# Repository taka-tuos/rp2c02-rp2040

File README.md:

# RP2C02 & RP2040 DevBoard

## 概要
RP2C02の限界が見たかったので作った

## 写真

## 部品
- 1 x Raspberry Pi Pico
- 1 x RP2C02
- 1 x Si5351Aモジュール(Adafruitタイプ、25MHz) or ピン互換の21.477272MHzモジュール(各自で作成)
- 1 x 2SA937
- 1 x 74HC573
- 1 x 62256 (<120ns)
- 2 x 100nF 2.54mm
- 1 x 22uF 5.0φ
- 1 x 470uF
- 1 x 150ohm
- 1 x 75ohm
- 1 x 820ohm
- 1 x RCAコネクタ

## なんでRP2040？
手元にあったのと流行りなので…

## レベル変換は？
- ADCピン以外は5.0Vまで耐えられるらしいので、それを信じることにした
- WRITEだけなら問題ない(割り込みピンはOpen-Drain駆動)

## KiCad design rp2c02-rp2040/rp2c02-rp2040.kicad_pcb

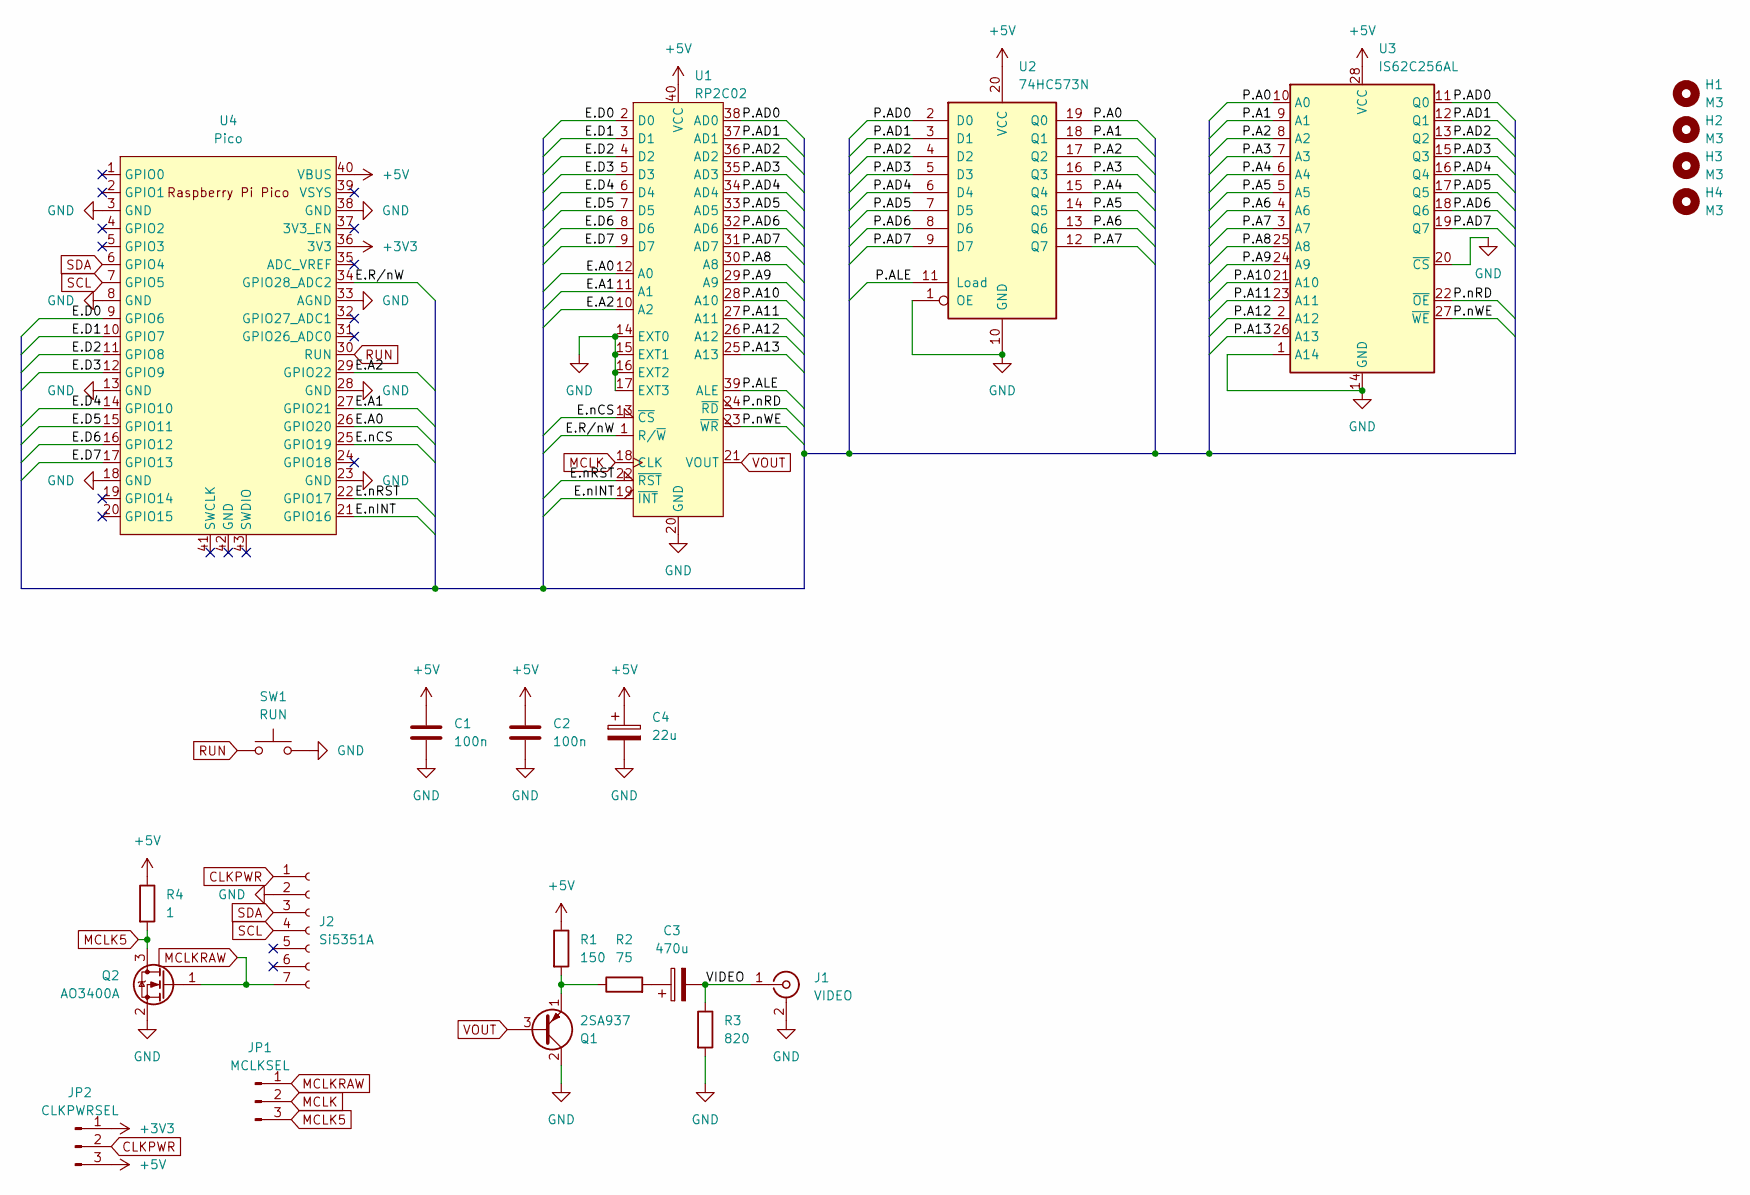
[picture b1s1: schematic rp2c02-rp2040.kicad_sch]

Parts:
C1, C2: 100n; C_Disc_D3.0mm_W1.6mm_P2.50mm
C3: 470u; CP_Radial_D10.0mm_P5.00mm
C4: 22u; CP_Radial_D5.0mm_P2.00mm
H1, H2, H3, H4: M3; MountingHole_3.2mm_M3
J1: VIDEO; CUI_RCJ-014
J2: Si5351A; PinSocket_1x07_P2.54mm_Vertical
JP1: MCLKSEL; PinHeader_1x03_P2.54mm_Vertical
JP2: CLKPWRSEL; PinHeader_1x03_P2.54mm_Vertical
Q1: 2SA937; PinSocket_1x03_P2.54mm_Vertical
Q2: AO3400A; SOT-23
R1: 150; R_Axial_DIN0207_L6.3mm_D2.5mm_P10.16mm_Horizontal
R2: 75; R_Axial_DIN0207_L6.3mm_D2.5mm_P10.16mm_Horizontal
R3: 820; R_Axial_DIN0207_L6.3mm_D2.5mm_P10.16mm_Horizontal
R4: 1; R_0805_2012Metric_Pad1.20x1.40mm_HandSolder
SW1: RUN; SW_PUSH_6mm
U1: RP2C02; DIP-40_W15.24mm_Socket
U2: 74HC573N; DIP-20_W7.62mm_Socket
U3: IS62C256AL; DIP-28_W15.24mm_Socket
U4: Pico; RPi_Pico_SMD_TH

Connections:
+3V3: JP2.1, U4.36 (3V3)
+5V: C1.1, C2.1, C4.1, JP2.3, R1.1, R4.1, U1.40 (VCC), U2.20 (VCC), U3.28 (VCC), U4.40 (VBUS)
/E.A0: U1.12 (A0), U4.26 (GPIO20)
/E.A1: U1.11 (A1), U4.27 (GPIO21)
/E.A2: U1.10 (A2), U4.29 (GPIO22)
/E.D0: U1.2 (D0), U4.9 (GPIO6)
/E.D1: U1.3 (D1), U4.10 (GPIO7)
/E.D2: U1.4 (D2), U4.11 (GPIO8)
/E.D3: U1.5 (D3), U4.12 (GPIO9)
/E.D4: U1.6 (D4), U4.14 (GPIO10)
/E.D5: U1.7 (D5), U4.15 (GPIO11)
/E.D6: U1.8 (D6), U4.16 (GPIO12)
/E.D7: U1.9 (D7), U4.17 (GPIO13)
/E.R/nW: U1.1 (R/~W), U4.34 (GPIO28_ADC2)
/E.nCS: U1.13 (~CS), U4.25 (GPIO19)
/E.nINT: U1.19 (~INT), U4.21 (GPIO16)
/E.nRST: U1.22 (~RST), U4.22 (GPIO17)
/P.A0: U2.19 (Q0), U3.10 (A0)
/P.A1: U2.18 (Q1), U3.9 (A1)
/P.A2: U2.17 (Q2), U3.8 (A2)
/P.A3: U2.16 (Q3), U3.7 (A3)
/P.A4: U2.15 (Q4), U3.6 (A4)
/P.A5: U2.14 (Q5), U3.5 (A5)
/P.A6: U2.13 (Q6), U3.4 (A6)
/P.A7: U2.12 (Q7), U3.3 (A7)
/P.A8: U1.30 (A8), U3.25 (A8)
/P.A9: U1.29 (A9), U3.24 (A9)
/P.A10: U1.28 (A10), U3.21 (A10)
/P.A11: U1.27 (A11), U3.23 (A11)
/P.A12: U1.26 (A12), U3.2 (A12)
/P.A13: U1.25 (A13), U3.26 (A13)
/P.AD0: U1.38 (AD0), U2.2 (D0), U3.11 (Q0)
/P.AD1: U1.37 (AD1), U2.3 (D1), U3.12 (Q1)
/P.AD2: U1.36 (AD2), U2.4 (D2), U3.13 (Q2)
/P.AD3: U1.35 (AD3), U2.5 (D3), U3.15 (Q3)
/P.AD4: U1.34 (AD4), U2.6 (D4), U3.16 (Q4)
/P.AD5: U1.33 (AD5), U2.7 (D5), U3.17 (Q5)
/P.AD6: U1.32 (AD6), U2.8 (D6), U3.18 (Q6)
/P.AD7: U1.31 (AD7), U2.9 (D7), U3.19 (Q7)
/P.ALE: U1.39 (ALE), U2.11 (Load)
/P.nRD: U1.24 (~RD), U3.22 (~OE)
/P.nWE: U1.23 (~WR), U3.27 (~WE)
/VIDEO: C3.2, J1.1 (In), R3.1
CLKPWR: J2.1, JP2.2
GND: C1.2, C2.2, C4.2, J1.2 (Ext), J2.2, Q1.2 (C), Q2.2 (S), R3.2, SW1.2, U1.14 (EXT0), U1.15 (EXT1), U1.16 (EXT2), U1.17 (EXT3), U1.20 (GND), U2.1 (OE), U2.10 (GND), U3.1 (A14), U3.14 (GND), U3.20 (~CS), U4.3 (GND), U4.8 (GND), U4.13 (GND), U4.18 (GND), U4.23 (GND), U4.28 (GND), U4.33 (AGND), U4.38 (GND)
MCLK: JP1.2, U1.18 (CLK)
MCLK5: JP1.3, Q2.3 (D), R4.2
MCLKRAW: J2.7, JP1.1, Q2.1 (G)
unnamed: C3.1, R2.2
unnamed: Q1.1 (E), R1.2, R2.1
RUN: SW1.1, U4.30 (RUN)
SCL: J2.4, U4.7 (GPIO5)
SDA: J2.3, U4.6 (GPIO4)
VOUT: Q1.3 (B), U1.21 (VOUT)

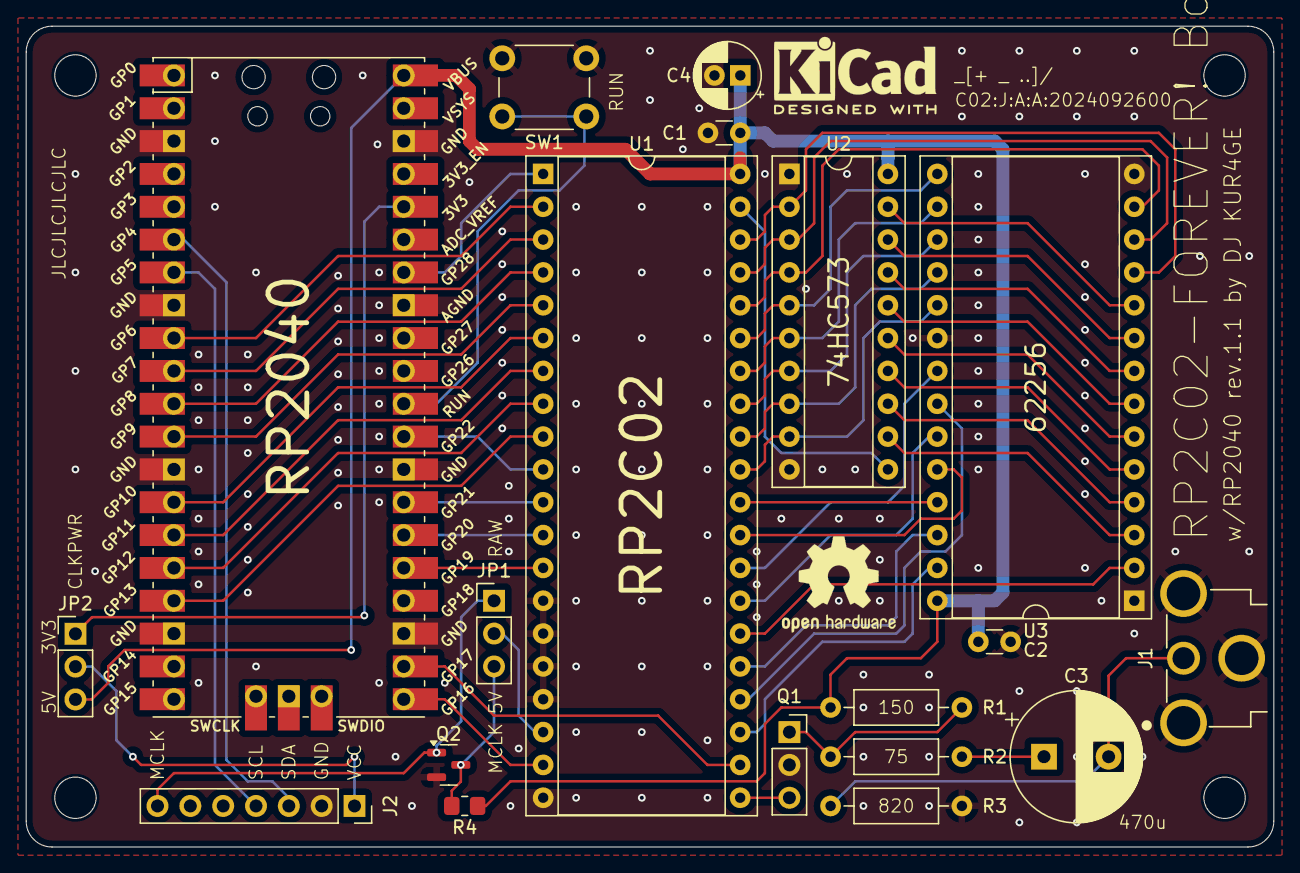
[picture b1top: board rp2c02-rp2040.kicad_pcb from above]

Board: 2 copper layers, 96.5 x 63.5 mm, 23 parts (0 on the bottom side), 54 nets.

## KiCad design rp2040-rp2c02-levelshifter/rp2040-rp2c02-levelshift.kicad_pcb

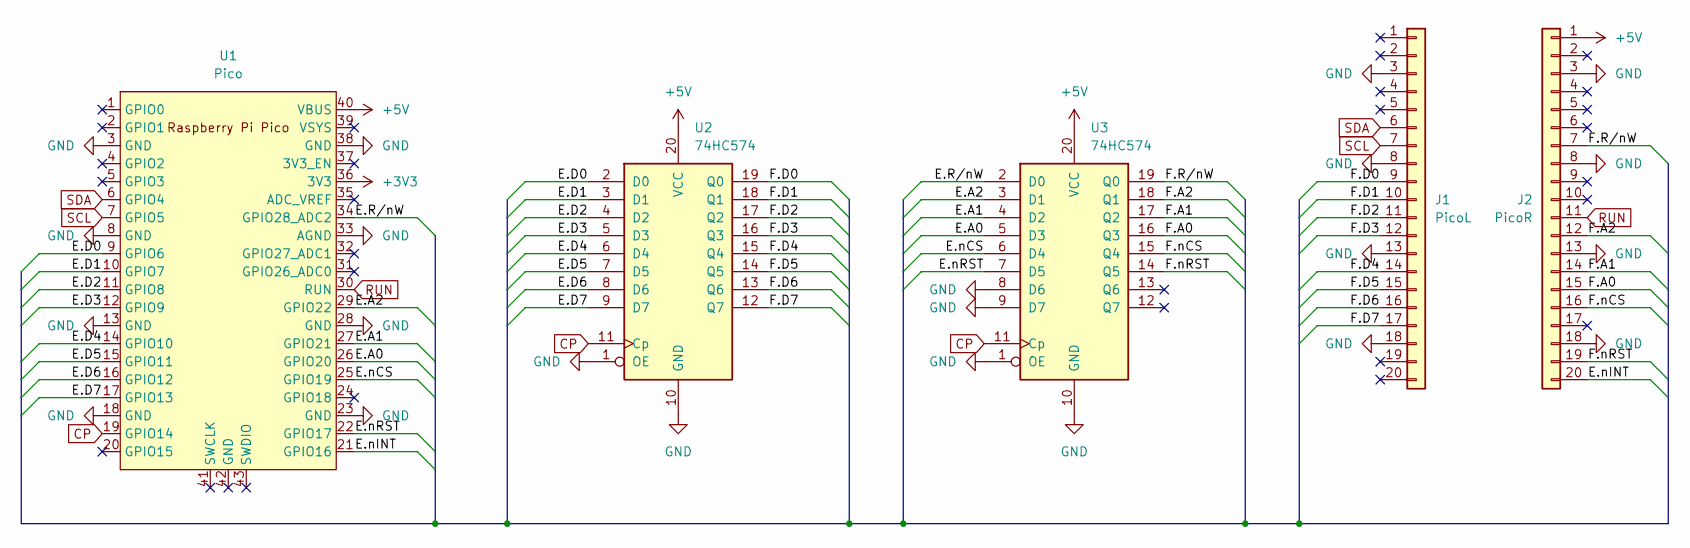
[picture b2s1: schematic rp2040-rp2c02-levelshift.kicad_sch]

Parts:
J1: PicoL; PinHeader_1x20_P2.54mm_Vertical
J2: PicoR; PinHeader_1x20_P2.54mm_Vertical
U1: Pico; RPi_Pico_SMD_TH
U2, U3: 74HC574; DIP-20_W7.62mm_Socket

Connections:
+3V3: U1.36 (3V3)
+5V: J2.1, U1.40 (VBUS), U2.20 (VCC), U3.20 (VCC)
/E.A0: U1.26 (GPIO20), U3.5 (D3)
/E.A1: U1.27 (GPIO21), U3.4 (D2)
/E.A2: U1.29 (GPIO22), U3.3 (D1)
/E.D0: U1.9 (GPIO6), U2.2 (D0)
/E.D1: U1.10 (GPIO7), U2.3 (D1)
/E.D2: U1.11 (GPIO8), U2.4 (D2)
/E.D3: U1.12 (GPIO9), U2.5 (D3)
/E.D4: U1.14 (GPIO10), U2.6 (D4)
/E.D5: U1.15 (GPIO11), U2.7 (D5)
/E.D6: U1.16 (GPIO12), U2.8 (D6)
/E.D7: U1.17 (GPIO13), U2.9 (D7)
/E.R/nW: U1.34 (GPIO28_ADC2), U3.2 (D0)
/E.nCS: U1.25 (GPIO19), U3.6 (D4)
/E.nINT: J2.20, U1.21 (GPIO16)
/E.nRST: U1.22 (GPIO17), U3.7 (D5)
/F.A0: J2.15, U3.16 (Q3)
/F.A1: J2.14, U3.17 (Q2)
/F.A2: J2.12, U3.18 (Q1)
/F.D0: J1.9, U2.19 (Q0)
/F.D1: J1.10, U2.18 (Q1)
/F.D2: J1.11, U2.17 (Q2)
/F.D3: J1.12, U2.16 (Q3)
/F.D4: J1.14, U2.15 (Q4)
/F.D5: J1.15, U2.14 (Q5)
/F.D6: J1.16, U2.13 (Q6)
/F.D7: J1.17, U2.12 (Q7)
/F.R/nW: J2.7, U3.19 (Q0)
/F.nCS: J2.16, U3.15 (Q4)
/F.nRST: J2.19, U3.14 (Q5)
CP: U1.19 (GPIO14), U2.11 (Cp), U3.11 (Cp)
GND: J1.3, J1.8, J1.13, J1.18, J2.3, J2.8, J2.13, J2.18, U1.3 (GND), U1.8 (GND), U1.13 (GND), U1.18 (GND), U1.23 (GND), U1.28 (GND), U1.33 (AGND), U1.38 (GND), U2.1 (OE), U2.10 (GND), U3.1 (OE), U3.8 (D6), U3.9 (D7), U3.10 (GND)
RUN: J2.11, U1.30 (RUN)
SCL: J1.7, U1.7 (GPIO5)
SDA: J1.6, U1.6 (GPIO4)

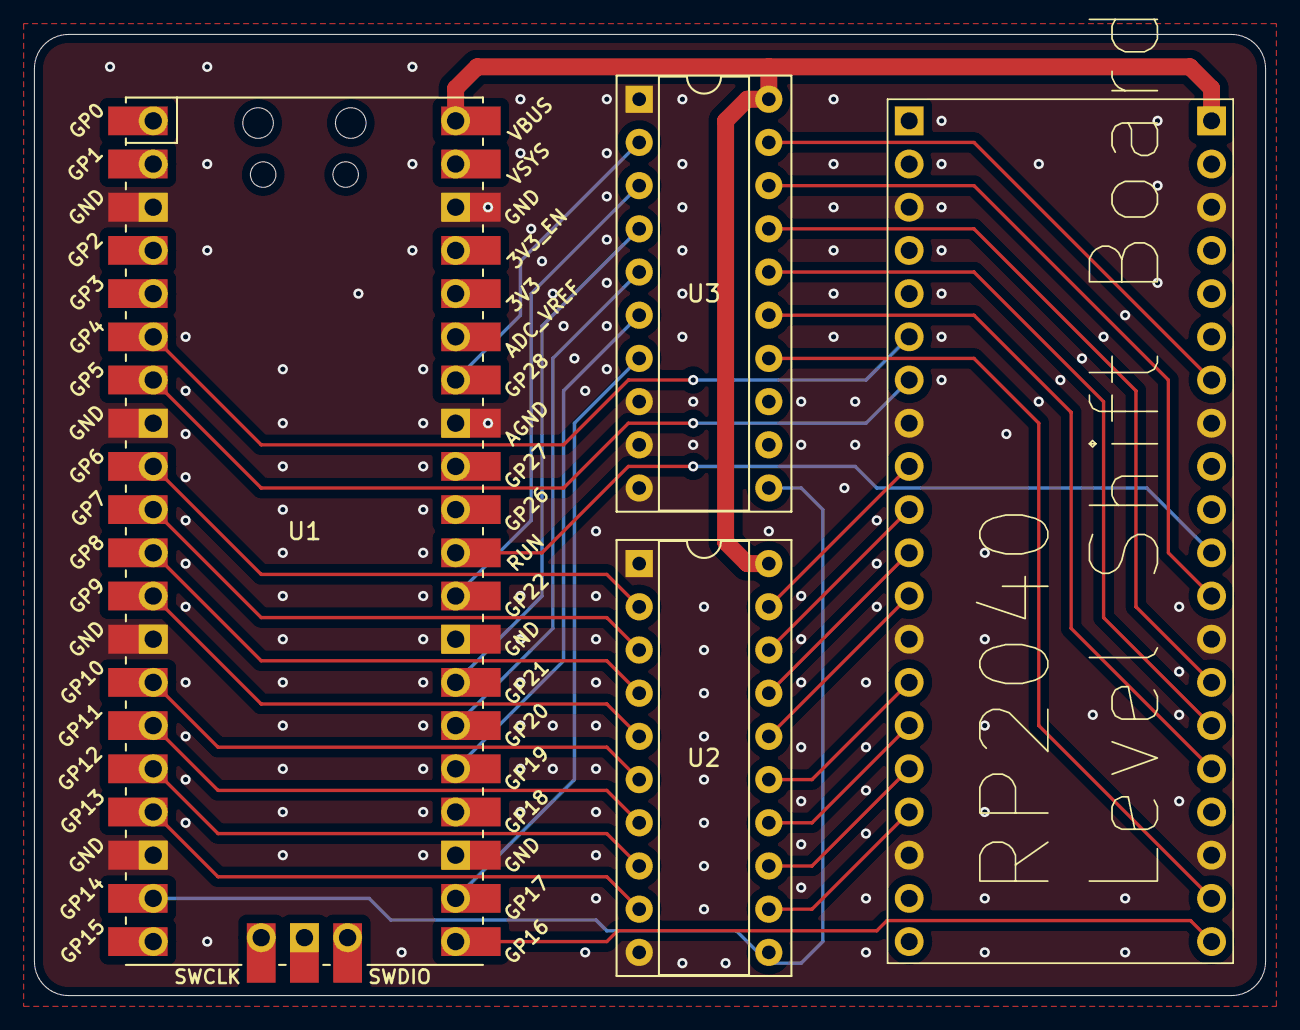
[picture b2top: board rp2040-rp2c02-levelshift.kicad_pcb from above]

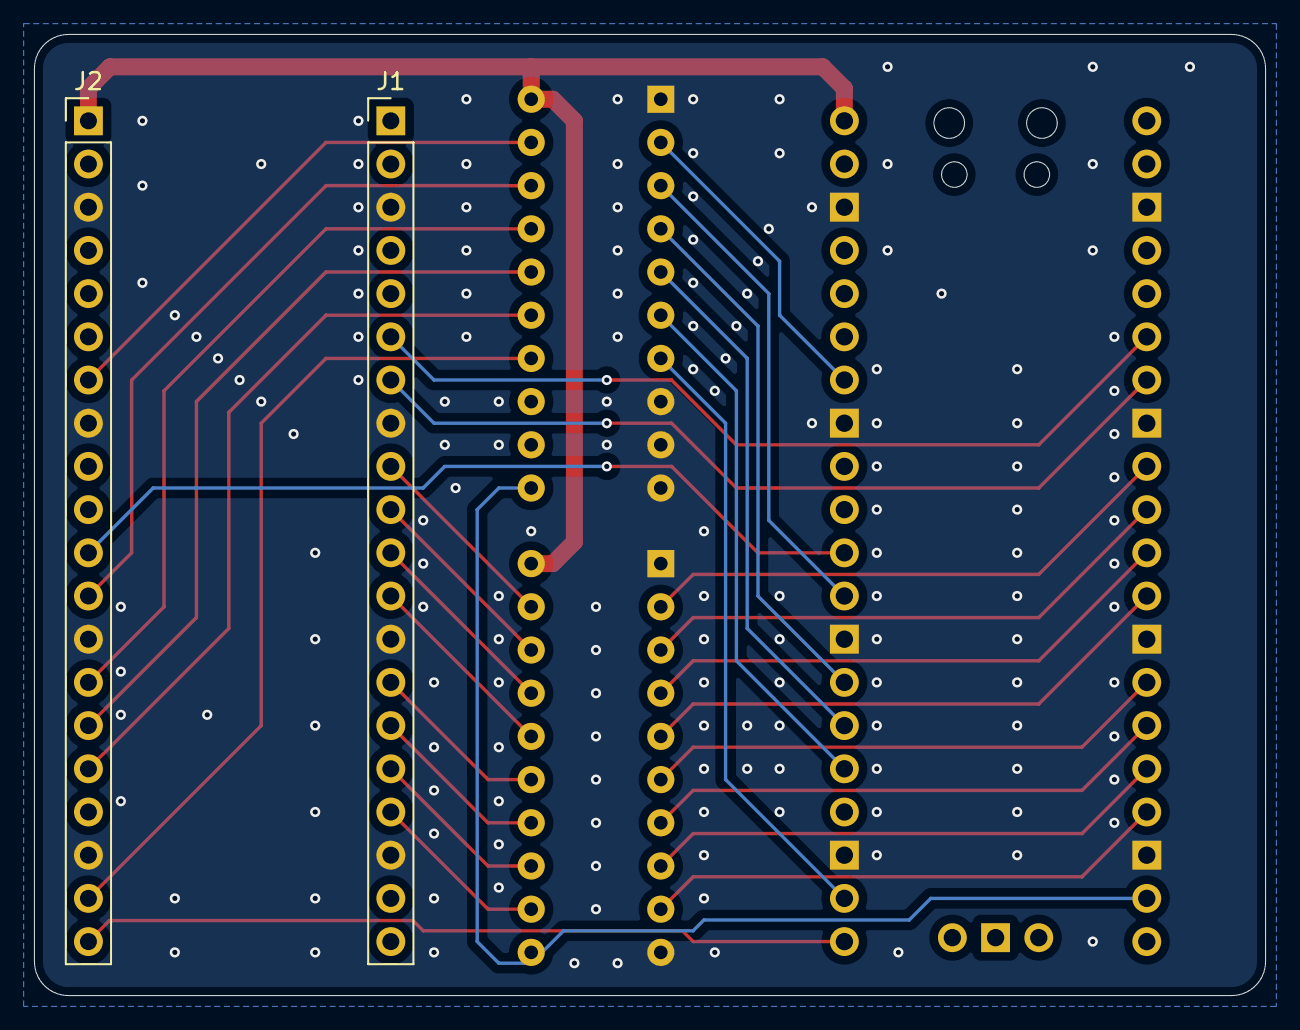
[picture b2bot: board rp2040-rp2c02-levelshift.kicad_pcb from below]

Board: 2 copper layers, 72.4 x 56.5 mm, 5 parts (2 on the bottom side), 35 nets.

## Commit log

2024-09-20 READMEとライセンスを追加
2024-09-26 レベルシフト版/レベルシフト基板追加、通常基板の2SA937ピン逆転修正
2024-09-27 74HC573に修正
2024-09-27 README更新
